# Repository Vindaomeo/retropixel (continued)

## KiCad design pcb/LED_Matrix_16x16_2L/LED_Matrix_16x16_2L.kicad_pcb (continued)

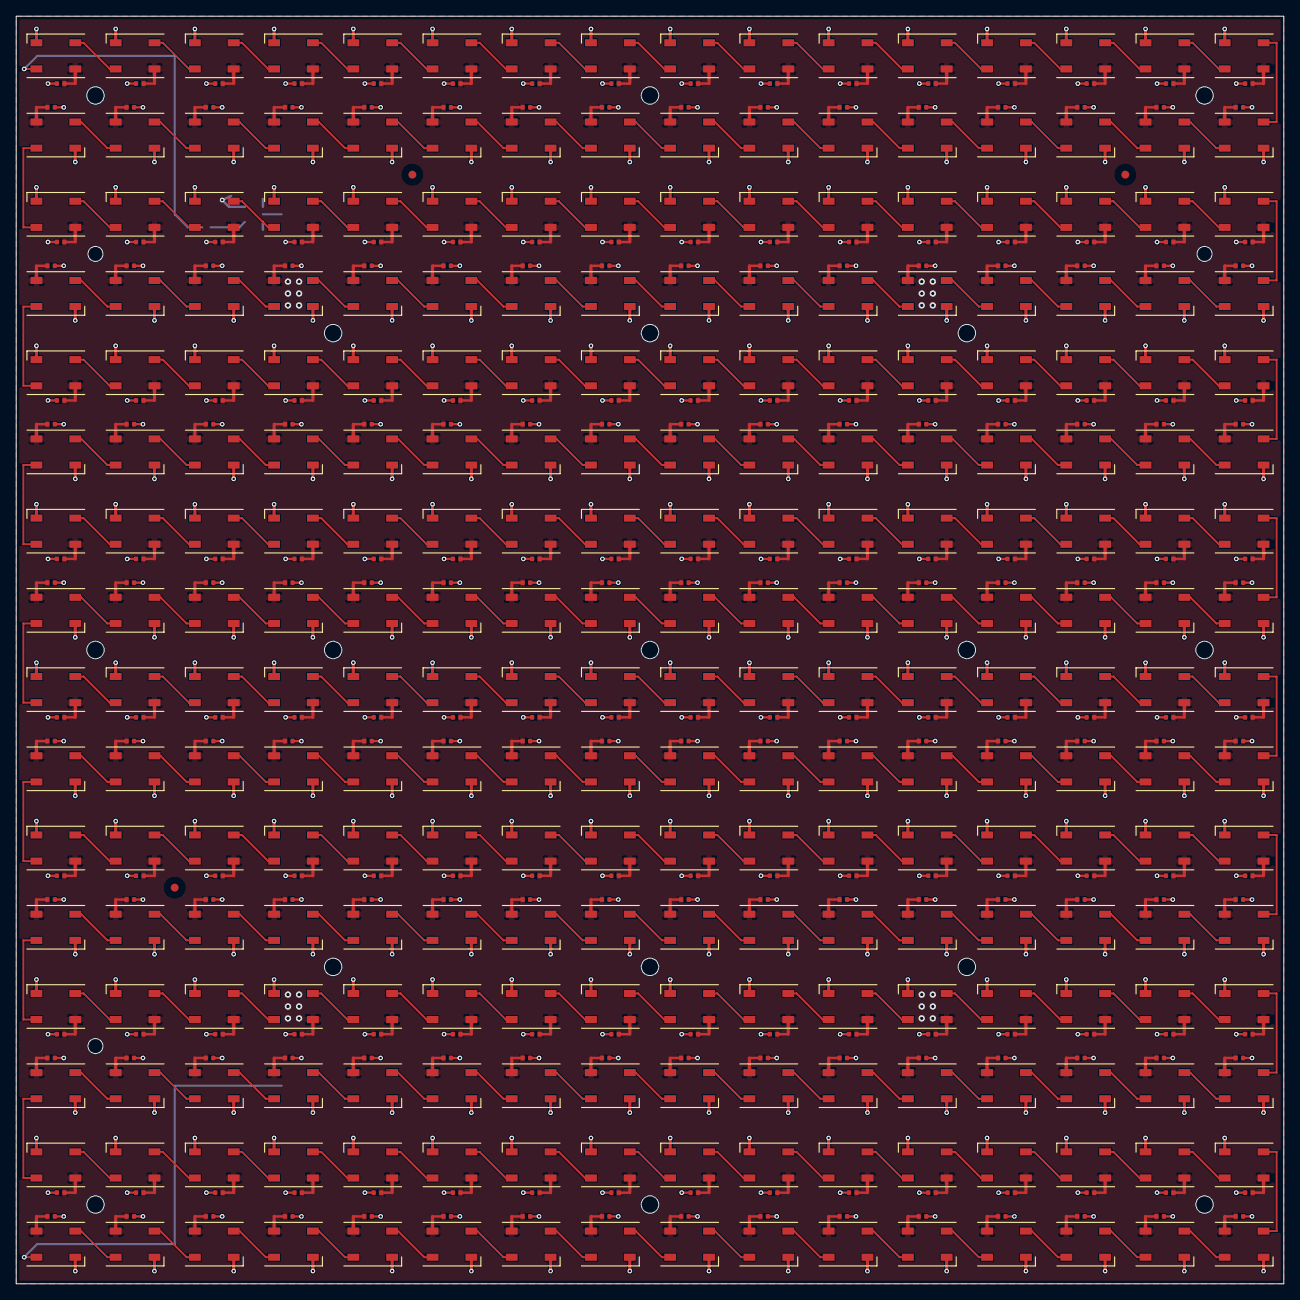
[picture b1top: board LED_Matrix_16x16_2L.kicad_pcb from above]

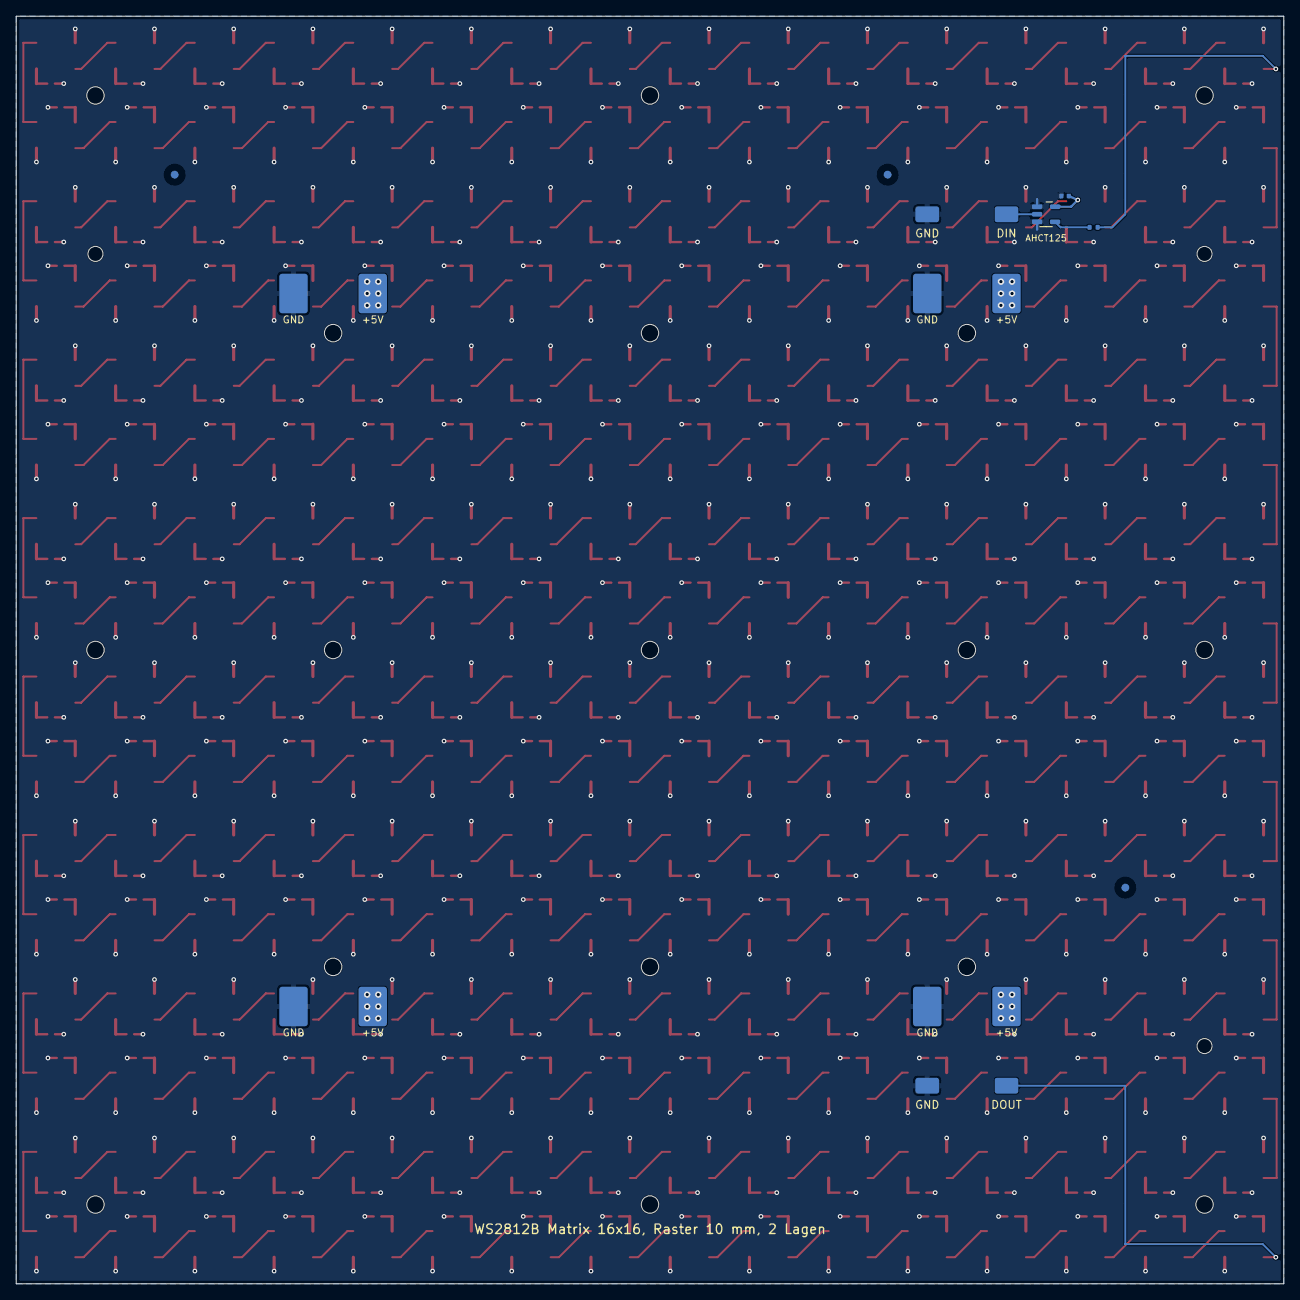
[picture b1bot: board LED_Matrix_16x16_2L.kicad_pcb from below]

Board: 2 copper layers, 160.0 x 160.0 mm, 553 parts (18 on the bottom side), 261 nets.

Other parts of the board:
H10, H11, H12, H13, H14, H15, H16, H17: Hole; NPTH_2.2mm
H18, H19, H20: Locate; NPTH_1.9mm

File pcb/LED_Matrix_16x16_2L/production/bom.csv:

Designator,Footprint,Quantity,Value,LCSC Part #
"C1, C10, C100, C101, C102, C103, C104, C105, C106, C107, C108, C109, C11, C110, C111, C112, C113, C114, C115, C116, C117, C118, C119, C12, C120, C121, C122, C123, C124, C125, C126, C127, C128, C129, C13, C130, C131, C132, C133, C134, C135, C136, C137, C138, C139, C14, C140, C141, C142, C143, C144, C145, C146, C147, C148, C149, C15, C150, C151, C152, C153, C154, C155, C156, C157, C158, C159, C16, C160, C161, C162, C163, C164, C165, C166, C167, C168, C169, C17, C170, C171, C172, C173, C174, C175, C176, C177, C178, C179, C18, C180, C181, C182, C183, C184, C185, C186, C187, C188, C189, C19, C190, C191, C192, C193, C194, C195, C196, C197, C198, C199, C2, C20, C200, C201, C202, C203, C204, C205, C206, C207, C208, C209, C21, C210, C211, C212, C213, C214, C215, C216, C217, C218, C219, C22, C220, C221, C222, C223, C224, C225, C226, C227, C228, C229, C23, C230, C231, C232, C233, C234, C235, C236, C237, C238, C239, C24, C240, C241, C242, C243, C244, C245, C246, C247, C248, C249, C25, C250, C251, C252, C253, C254, C255, C256, C257, C26, C27, C28, C29, C3, C30, C31, C32, C33, C34, C35, C36, C37, C38, C39, C4, C40, C41, C42, C43, C44, C45, C46, C47",0402,200,100nF,C1525
"C48, C49, C5, C50, C51, C52, C53, C54, C55, C56, C57, C58, C59, C6, C60, C61, C62, C63, C64, C65, C66, C67, C68, C69, C7, C70, C71, C72, C73, C74, C75, C76, C77, C78, C79, C8, C80, C81, C82, C83, C84, C85, C86, C87, C88, C89, C9, C90, C91, C92, C93, C94, C95, C96, C97, C98, C99",0402,57,100nF,C1525
"D1, D10, D100, D101, D102, D103, D104, D105, D106, D107, D108, D109, D11, D110, D111, D112, D113, D114, D115, D116, D117, D118, D119, D12, D120, D121, D122, D123, D124, D125, D126, D127, D128, D129, D13, D130, D131, D132, D133, D134, D135, D136, D137, D138, D139, D14, D140, D141, D142, D143, D144, D145, D146, D147, D148, D149, D15, D150, D151, D152, D153, D154, D155, D156, D157, D158, D159, D16, D160, D161, D162, D163, D164, D165, D166, D167, D168, D169, D17, D170, D171, D172, D173, D174, D175, D176, D177, D178, D179, D18, D180, D181, D182, D183, D184, D185, D186, D187, D188, D189, D19, D190, D191, D192, D193, D194, D195, D196, D197, D198, D199, D2, D20, D200, D201, D202, D203, D204, D205, D206, D207, D208, D209, D21, D210, D211, D212, D213, D214, D215, D216, D217, D218, D219, D22, D220, D221, D222, D223, D224, D225, D226, D227, D228, D229, D23, D230, D231, D232, D233, D234, D235, D236, D237, D238, D239, D24, D240, D241, D242, D243, D244, D245, D246, D247, D248, D249, D25, D250, D251, D252, D253, D254, D255, D256, D26, D27, D28, D29, D3, D30, D31, D32, D33, D34, D35, D36, D37, D38, D39, D4, D40, D41, D42, D43, D44, D45, D46, D47, D48",LED_WS2812B_PLCC4_5.0x5.0mm_P3.2mm,200,WS2812B,C2843785
"D49, D5, D50, D51, D52, D53, D54, D55, D56, D57, D58, D59, D6, D60, D61, D62, D63, D64, D65, D66, D67, D68, D69, D7, D70, D71, D72, D73, D74, D75, D76, D77, D78, D79, D8, D80, D81, D82, D83, D84, D85, D86, D87, D88, D89, D9, D90, D91, D92, D93, D94, D95, D96, D97, D98, D99",LED_WS2812B_PLCC4_5.0x5.0mm_P3.2mm,56,WS2812B,C2843785
J1,SolderPad_3x2mm,1,DIN,
"J10, J12, J6, J8",SolderPad_3.6x5mm,4,GND,
"J11, J5, J7, J9",SolderPad_3.6x5mm,4,+5V,
"J2, J4",SolderPad_3x2mm,2,GND,
J3,SolderPad_3x2mm,1,DOUT,
R1,0402,1,33R,C25105
U1,SOT-23-5,1,74AHCT1G125,C7484
